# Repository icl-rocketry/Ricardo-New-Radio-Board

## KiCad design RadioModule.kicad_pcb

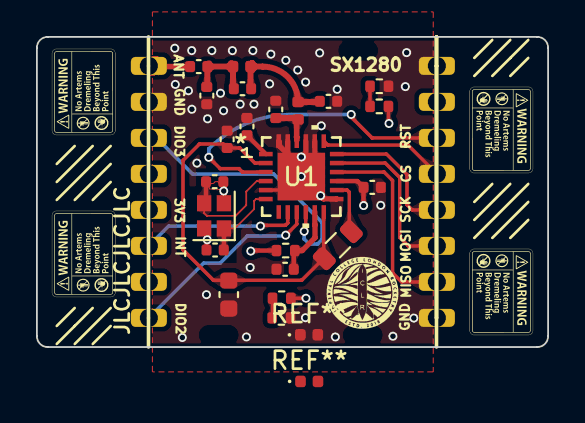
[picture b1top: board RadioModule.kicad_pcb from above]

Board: 4 copper layers, 28.4 x 17.2 mm, 38 parts (0 on the bottom side), 22 nets.

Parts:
3.3VLED1: RED_LED; R_0402_1005Metric
3V3LED1: BLUE_LED; R_0402_1005Metric
C1, C2: 10nF; C_0402_1005Metric
C3, C4: 4pF; C_0402_1005Metric
C5, C8: 100nF; C_0402_1005Metric
C6: 470nF; C_0603_1608Metric
C7: 0.8pF; C_0402_1005Metric
C11, C13: 1.2pF; C_0402_1005Metric
C12: 0.5pF; C_0402_1005Metric
C14: 100pF; C_0402_1005Metric
J1, J2, J3, J4, J5, J6, J7, J8, J9, J10, J11, J12, J13, J14, J15, J16: Conn_01x01_Pin; SolderWirePad_1x01_SMD_1x2mm
L1: 15uH; L_0805_2012Metric
L2: 3nH; L_0402_1005Metric
L3: 2.5nH; L_0402_1005Metric
R1: 0R; R_0402_1005Metric
R2: 470; R_0402_1005Metric
R3: 3k; R_0402_1005Metric
U1: SX1280IMLTRT; QFN24_4X4_SEM
Y1: ABM13W-52.0MHz; Crystal_SMD_2016-4Pin_2.0x1.6mm

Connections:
3V3: 3.3VLED1.2 (A), C8.2, J5.1, R1.1, R2.2, U1.15 (VBAT)
/V_DCC: C2.1, C6.1, L1.1, U1.2 (VDD_INN), U1.12 (DCC_FB)
/V_DCC2: L1.2, U1.14 (DCC_SW)
/V_PA: C1.1, U1.1 (VR_PA)
/XTA: C4.2, U1.4 (XTA), Y1.3
/XTB_Reference Oscillator: C3.2, U1.6 (XTB), Y1.1
ANT: C14.1, J1.1
CS: J12.1, U1.19 (NSS_CTS)
DIO2: J8.1, U1.9 (DIO2)
DIO3: J3.1, U1.10 (DIO3)
GND: 3V3LED1.1 (K), C1.2, C2.2, C3.1, C4.1, C5.2, C6.2, C7.2, C8.1, C11.2, C13.2, J2.1, J9.1, J16.1, R3.1, U1.5 (GND), U1.13 (GND), U1.20 (GND), U1.21 (GND), U1.23 (GND), U1.24 (GND), U1.25 (GND), Y1.2, Y1.4
INT: J6.1, U1.8 (DIO1)
MISO: J15.1, U1.16 (MISO_TX)
MOSI: J14.1, U1.17 (MOSI_RX)
NRST: J11.1, U1.3 (NRESET)
unnamed: 3.3VLED1.1 (K), R3.2
unnamed: 3V3LED1.2 (A), R2.1
unnamed: C11.1, C12.2, L2.2, L3.1
unnamed: C12.1, C13.1, C14.2, L3.2
unnamed: C7.1, L2.1, U1.22 (RFIO)
unnamed: C5.1, R1.2, U1.11 (VBAT_IO)
SCK: J13.1, U1.18 (SCK_RTSN)

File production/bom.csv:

Designator,Footprint,Quantity,Value,LCSC Part #
"_3, _2, ",,3,,
3.3VLED1,0402,1,RED_LED,
3V3LED1,0402,1,BLUE_LED,
"C1, C2",0402,2,10nF,
"C11, C13",0402,2,1.2pF,
C12,0402,1,0.5pF,
C14,0402,1,100pF,
"C3, C4",0402,2,4pF,
"C5, C8",0402,2,100nF,
C6,0603,1,470nF,
C7,0402,1,0.8pF,
"J1, J10, J11, J12, J13, J14, J15, J16, J2, J3, J4, J5, J6, J7, J8, J9",SolderWirePad_1x01_SMD_1x2mm,16,Conn_01x01_Pin,
L1,0805,1,15uH,
L2,0402,1,3nH,
L3,0402,1,2.5nH,
R1,0402,1,0R,
R2,0402,1,470,
R3,0402,1,3k,
U1,QFN24_4X4_SEM,1,SX1280IMLTRT,
Y1,Crystal_SMD_2016-4Pin_2.0x1.6mm,1,ABM13W-52.0MHz,

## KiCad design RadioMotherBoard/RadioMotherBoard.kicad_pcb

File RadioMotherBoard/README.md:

# Ricardo-BoardTemplate
Board template including the required components for an ESP32S3 as well as CAN and USB. This is the bare minimum needed for boards in the ricardo ecosystem. To use, place the Ricardo-BoardTemplate folder in your KiCad user templates folder. 
By default, this folder is:
Windows - %USERPROFILE%/Documents/KiCad/6.0/template

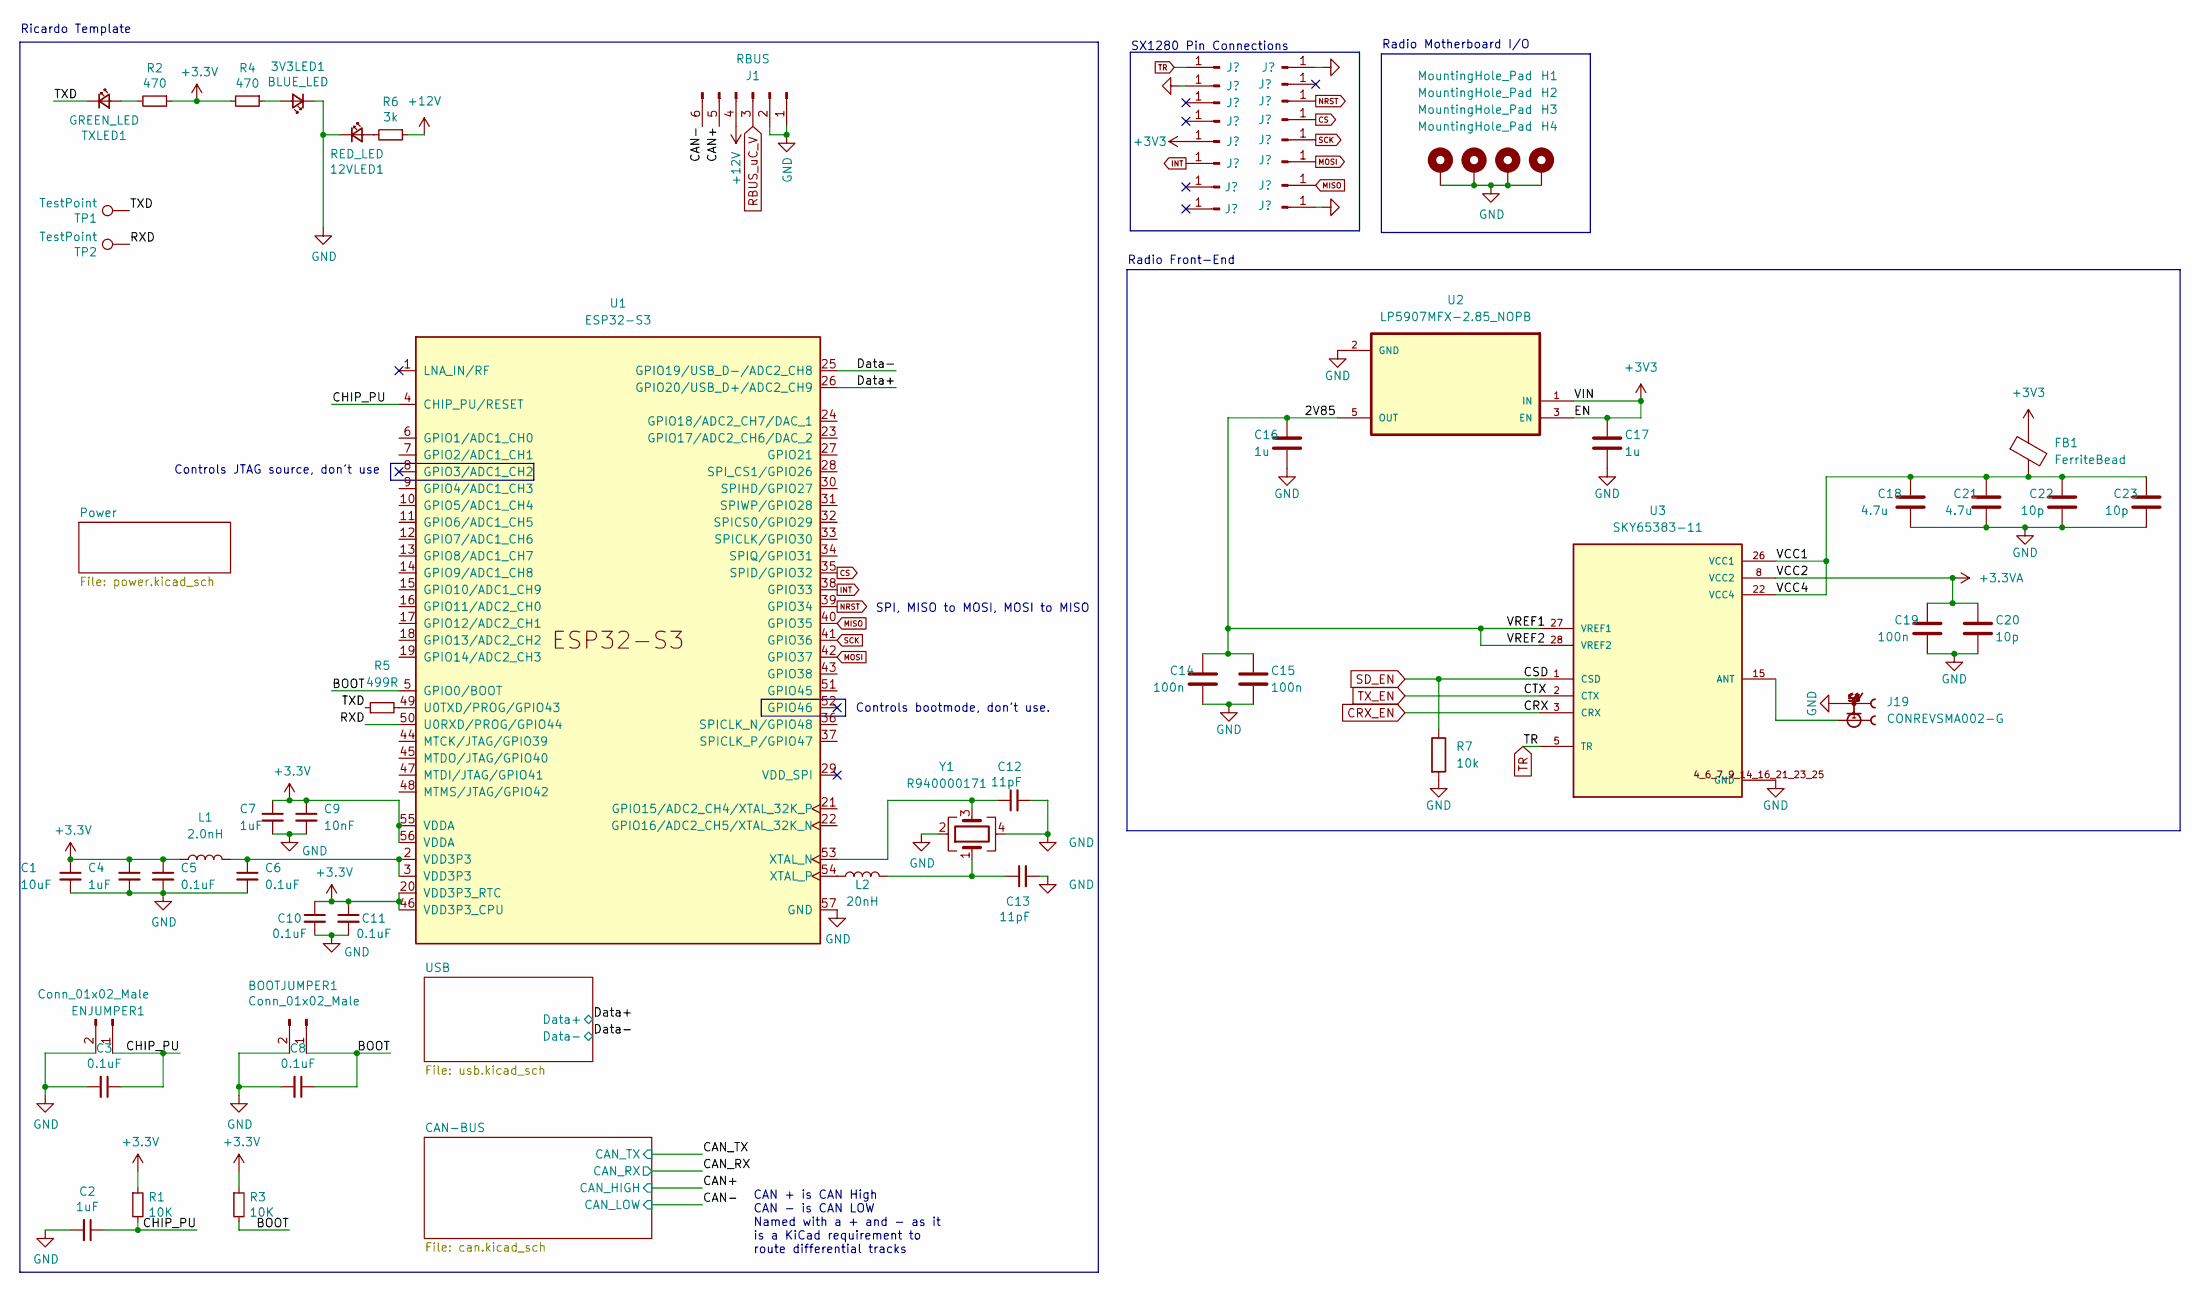
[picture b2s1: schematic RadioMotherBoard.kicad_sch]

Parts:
3V3LED1: BLUE_LED; BEADC1608X95N
12VLED1: RED_LED; R_0402_1005Metric
BOOTJUMPER1: Conn_01x02_Male; PinHeader_1x02_P2.54mm_Vertical
C1: 10uF; C_0402_1005Metric
C2, C4, C7: 1uF; C_0402_1005Metric
C3, C5, C6, C8, C10, C11: 0.1uF; C_0402_1005Metric
C9: 10nF; C_0402_1005Metric
C12, C13: 11pF; C_0402_1005Metric
C14, C15, C19: 100n; C_0402_1005Metric
C16, C17: 1u; C_0402_1005Metric
C18, C21: 4.7u; C_0402_1005Metric
C20, C22, C23: 10p; C_0402_1005Metric
ENJUMPER1: Conn_01x02_Male; PinHeader_1x02_P2.54mm_Vertical
FB1: FerriteBead; BEADC1608X95N
H1, H2, H3, H4: MountingHole_Pad; MountingHole_3.2mm_M3_DIN965_Pad
J1: RBUS; Molex_Mini-Fit_Jr_5566-06A_2x03_P4.20mm_Vertical
J2, J3, J4, J5, J6, J7, J8, J9, J10, J11, J12, J13, J14, J15, J16, J17: Conn_01x01_Pin; PinHeader_1x01_P1.00mm_Vertical
J19: CONREVSMA002-G; LINX_CONREVSMA002-G
L1: 2.0nH; L_0402_1005Metric
L2: 20nH; L_0402_1005Metric
R1, R3: 10K; R_0402_1005Metric
R2, R4: 470; R_0402_1005Metric
R5: 499R; R_0402_1005Metric
R6: 3k; R_0402_1005Metric
R7: 10k; R_0402_1005Metric
TP1, TP2: TestPoint; TestPoint_Pad_D1.0mm
TXLED1: GREEN_LED; R_0402_1005Metric
U1: ESP32-S3; QFN40P700X700X90-57N
U2: LP5907MFX-2.85_NOPB; SOT95P280X145-5N
U3: SKY65383-11; IC_SKY65383-11; PARTREV 202668G
Y1: R940000171; Crystal_SMD_2016-4Pin_2.0x1.6mm

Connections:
+3.3VA: C19.1, C20.1, U3.8 (VCC2)
+12V: J1.4, R6.1
/2V85: C14.1, C15.1, C16.1, U2.5 (OUT), U3.27 (VREF1), U3.28 (VREF2)
/BOOT: BOOTJUMPER1.1, C8.1, R3.2, U1.5 (GPIO0/BOOT)
/CAN+: J1.5; also elsewhere on the board
/CAN-: J1.6; also elsewhere on the board
/CHIP_PU: C2.1, C3.1, ENJUMPER1.1, R1.2, U1.4 (CHIP_PU/RESET)
/Data+: U1.26 (GPIO20/USB_D+/ADC2_CH9); also elsewhere on the board
/Data-: U1.25 (GPIO19/USB_D-/ADC2_CH8); also elsewhere on the board
/RXD: TP2.1, U1.50 (U0RXD/PROG/GPIO44)
/TXD: R5.1, TP1.1, TXLED1.1 (K)
/VCC1: C18.1, C21.1, C22.1, C23.1, FB1.2, U3.22 (VCC4), U3.26 (VCC1)
CRX_EN: U3.3 (CRX)
CS: J13.1, U1.35 (SPID/GPIO32)
GND: 3V3LED1.1 (K), 12VLED1.1 (K), BOOTJUMPER1.2, C1.2, C2.2, C3.2, C4.2, C5.2, C6.2, C7.2, C8.2, C9.2, C10.2, C11.2, C12.2, C13.2, C14.2, C15.2, C16.2, C17.2, C18.2, C19.2, C20.2, C21.2, C22.2, C23.2, ENJUMPER1.2, H1.1, H2.1, H3.1, H4.1, J1.1, J1.2, J3.1, J10.1, J17.1, J19.S1, J19.S2, J19.S3, J19.S4, R7.2, U1.57 (GND), U2.2 (GND), U3.4_6_7_9_14_16_21_23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 (GND), Y1.2, Y1.4; also elsewhere on the board
INT: J7.1, U1.38 (GPIO33)
MISO: J16.1, U1.40 (GPIO35)
MOSI: J15.1, U1.42 (GPIO37)
NRST: J12.1, U1.39 (GPIO34)
unnamed: 3V3LED1.2 (A), R4.1
unnamed: 12VLED1.2 (A), R6.2
unnamed: C6.1, L1.2, U1.2 (VDD3P3), U1.3 (VDD3P3)
unnamed: C13.1, L2.2, Y1.1
unnamed: R2.2, TXLED1.2 (A)
unnamed: R5.2, U1.49 (U0TXD/PROG/GPIO43)
unnamed: C12.1, U1.53 (XTAL_N), Y1.3
unnamed: L2.1, U1.54 (XTAL_P)
unnamed: J19.1, U3.15 (ANT)
RBUS_uC_V: J1.3; also elsewhere on the board
SCK: J14.1, U1.41 (GPIO36)
SD_EN: R7.1, U3.1 (CSD)
TR: J2.1, U3.5 (TR)
TX_EN: U3.2 (CTX)

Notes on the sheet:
Controls bootmode, don't use.
Ricardo Template
CAN + is CAN High CAN - is CAN LOW Named with a + and - as it is a KiCad requirement to route differential tracks
Radio Front-End
Controls JTAG source, don't use
SPI, MISO to MOSI, MOSI to MISO
Radio Motherboard I/O
SX1280 Pin Connections

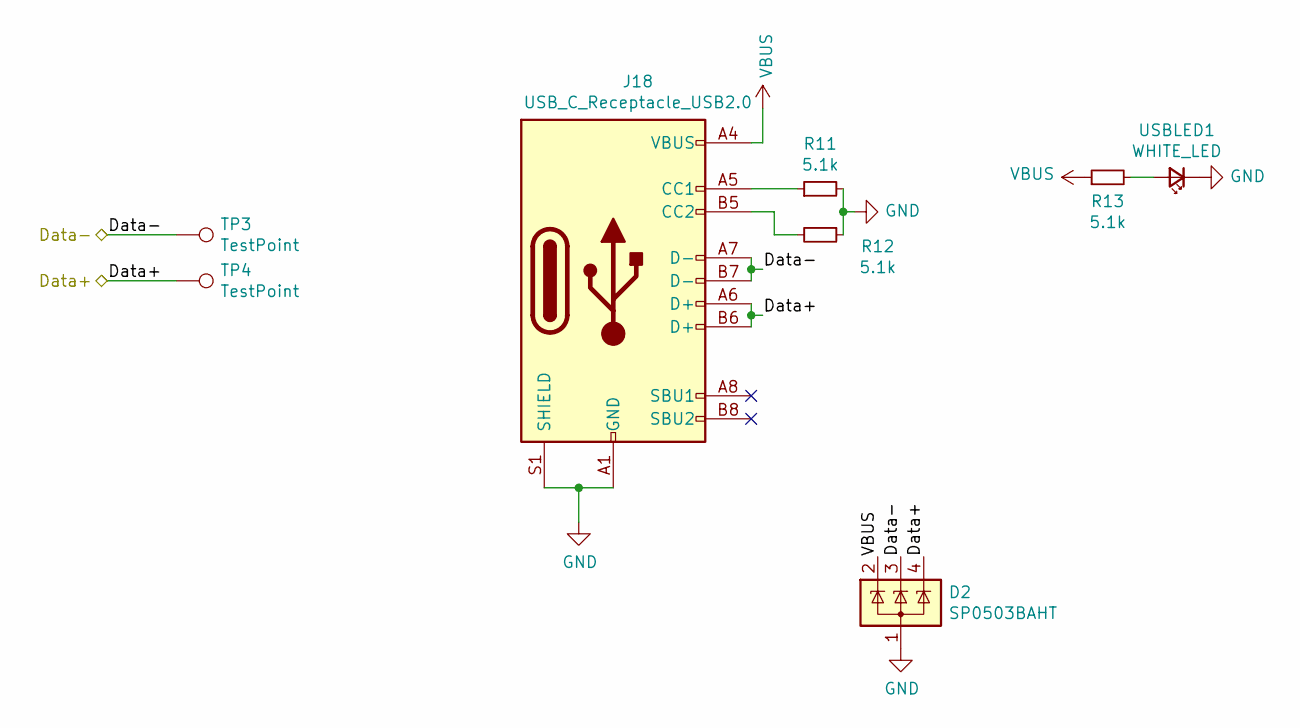
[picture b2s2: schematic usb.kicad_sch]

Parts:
D2: SP0503BAHT; SOT-143
J18: USB_C_Receptacle_USB2.0; USB_C_Receptacle_Palconn_UTC16-G
R11, R12, R13: 5.1k; R_0402_1005Metric
TP3, TP4: TestPoint; TestPoint_Pad_D1.0mm
USBLED1: WHITE_LED; R_0402_1005Metric

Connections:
/Data+: D2.4 (K), J18.A6 (D+), J18.B6 (D+), TP4.1; also elsewhere on the board
/Data-: D2.3 (K), J18.A7 (D-), J18.B7 (D-), TP3.1; also elsewhere on the board
GND: D2.1 (A), J18.A1 (GND), J18.A12 (GND), J18.B1 (GND), J18.B12 (GND), J18.S1 (SHIELD), R11.2, R12.1, USBLED1.1 (K); also elsewhere on the board
unnamed: J18.A5 (CC1), R11.1
unnamed: J18.B5 (CC2), R12.2
unnamed: R13.2, USBLED1.2 (A)
VBUS: D2.2 (K), J18.A4 (VBUS), J18.A9 (VBUS), J18.B4 (VBUS), J18.B9 (VBUS), R13.1; also elsewhere on the board

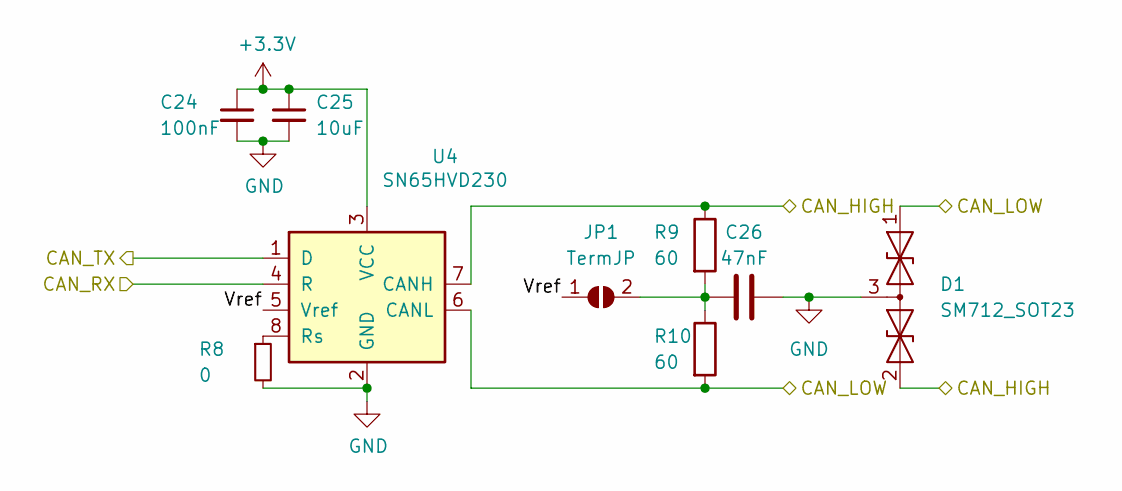
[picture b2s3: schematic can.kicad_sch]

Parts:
C24: 100nF; C_0402_1005Metric
C25: 10uF; C_0402_1005Metric
C26: 47nF; C_0402_1005Metric
D1: SM712_SOT23; SOT-23
JP1: TermJP; SolderJumper-2_P1.3mm_Open_RoundedPad1.0x1.5mm
R8: 0; R_0603_1608Metric
R9, R10: 60; R_0603_1608Metric
U4: SN65HVD230; SOIC-8_3.9x4.9mm_P1.27mm

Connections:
/CAN+: D1.2 (A2), R9.1, U4.7 (CANH); also elsewhere on the board
/CAN-: D1.1 (A1), R10.2, U4.6 (CANL); also elsewhere on the board
/CAN-BUS/Vref: JP1.1 (A), U4.5 (Vref)
/CAN_RX: U4.4 (R)
/CAN_TX: U4.1 (D)
GND: C24.2, C25.2, C26.2, D1.3 (common), R8.2, U4.2 (GND); also elsewhere on the board
unnamed: C26.1, JP1.2 (B), R9.2, R10.1
unnamed: R8.1, U4.8 (Rs)

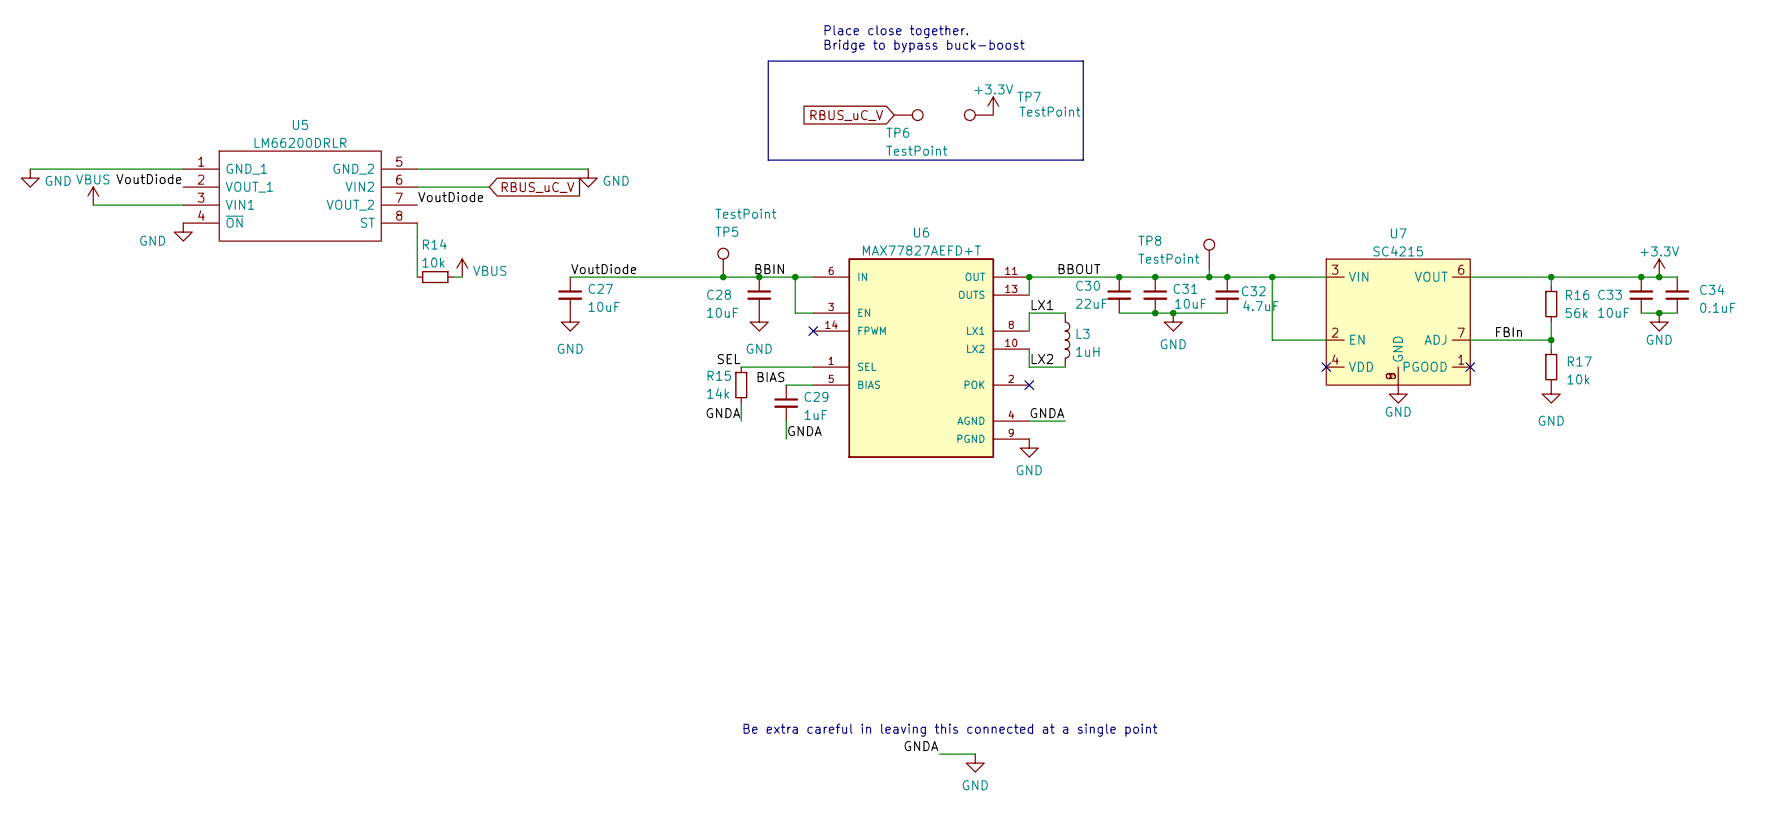
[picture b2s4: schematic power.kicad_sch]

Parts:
C27, C31, C33: 10uF; C_0402_1005Metric
C28: 10uF; C_0603_1608Metric
C29: 1uF; C_0402_1005Metric
C30: 22uF; C_0603_1608Metric
C32: 4.7uF; C_0402_1005Metric
C34: 0.1uF; C_0402_1005Metric
L3: 1uH; L_0805_2012Metric
R14, R17: 10k; R_0402_1005Metric
R15: 14k; R_0402_1005Metric
R16: 56k; R_0402_1005Metric
TP5, TP6, TP7, TP8: TestPoint; TestPoint_Pad_D1.5mm
U5: LM66200DRLR; SOTFL50P160X60-8N; Manufacturer_Part_Number LM66200DRLR; Mouser Part Number 595-LM66200DRLR
U6: MAX77827AEFD+T; CONV_MAX77827AEFD+T; PARTREV B
U7: SC4215; SOIC127P599X175-9N

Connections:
/Power/BBIN: C27.1, C28.1, TP5.1, U5.2 (VOUT_1), U5.7 (VOUT_2), U6.3 (EN), U6.6 (IN)
/Power/BBOUT: C30.1, C31.1, C32.1, TP8.1, U6.11 (OUT), U6.13 (OUTS), U7.2 (EN), U7.3 (VIN)
/Power/BIAS: C29.1, U6.5 (BIAS)
/Power/FBIn: R16.2, R17.1, U7.7 (ADJ)
/Power/LX1: L3.1, U6.8 (LX1)
/Power/LX2: L3.2, U6.10 (LX2)
/Power/SEL: R15.1, U6.1 (SEL)
GND: C27.2, C28.2, C29.2, C30.2, C31.2, C32.2, C33.1, C34.1, R15.2, R17.2, U5.1 (GND_1), U5.4 (~ON), U5.5 (GND_2), U6.4 (AGND), U6.9 (PGND), U7.8 (GND), U7.9 (GND); also elsewhere on the board
unnamed: R14.2, U5.8 (ST)
RBUS_uC_V: TP6.1, U5.6 (VIN2); also elsewhere on the board
VBUS: R14.1, U5.3 (VIN1); also elsewhere on the board

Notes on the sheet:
Place close together. Bridge to bypass buck-boost
Be extra careful in leaving this connected at a single point

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
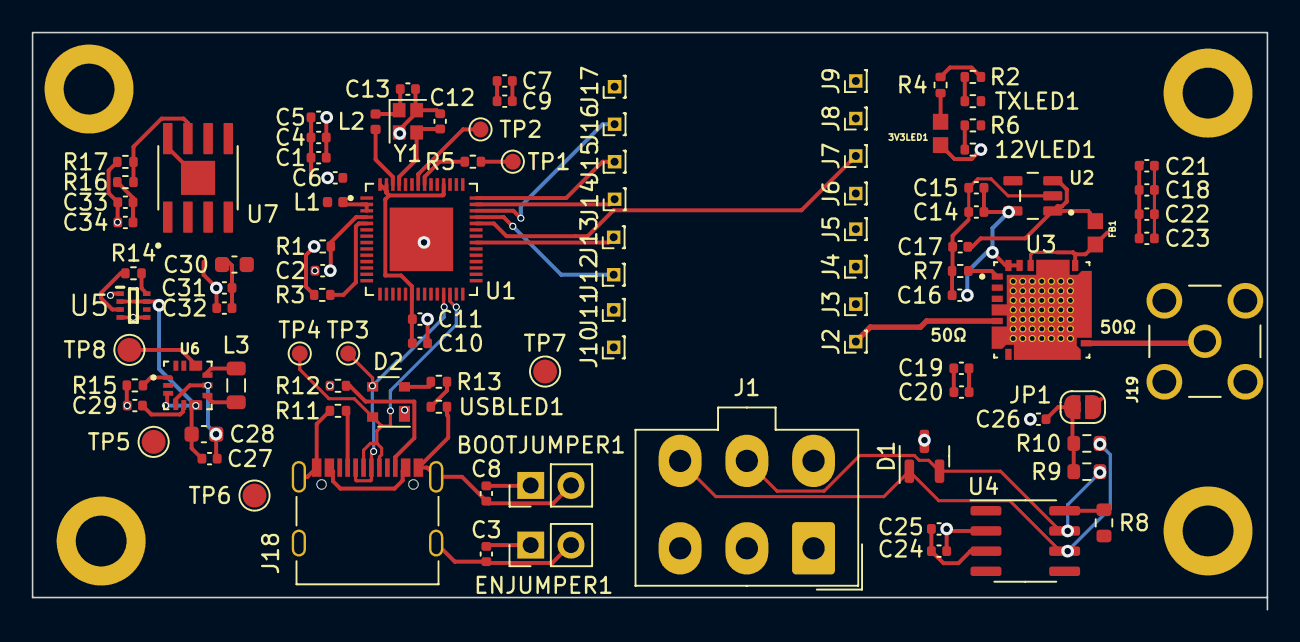
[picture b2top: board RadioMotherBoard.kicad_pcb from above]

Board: 4 copper layers, 77.7 x 36.3 mm, 103 parts (0 on the bottom side), 47 nets.

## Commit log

2023-12-12 Added RadioModule schematic
2023-12-13 Finished Radio Module Schematic
2023-12-21 Radio Schematic Update 1
2023-12-27 Radio Module Update 2
2024-01-21 Added project files for radio motherboard.
2024-01-21 Added Radio Front-End Schematic
2024-02-06 Rough PCB Design
2024-02-20 Post board review updated Radio Module
2024-02-20 Added 50 ohm lines
2024-02-20 Board rearrange
2024-02-28 Post Board Review Update
2024-02-29 Artem Review Changes
2024-02-29 lets try that again
2024-03-02 made it less clapped
2024-03-04 Added silkscreen and changed pi filter component values
2024-03-05 Hopefully final commit
2024-03-08 looks good
2024-04-19 Dora the LoRa Module
2024-04-28 Final Commit V1.0
2024-04-28 Moved a via
2024-04-28 Crystal Caps sized
2024-04-28 Put silkscreen on the back too
2024-04-28 actual final commit hopefully
2024-04-28 radio module ordering
